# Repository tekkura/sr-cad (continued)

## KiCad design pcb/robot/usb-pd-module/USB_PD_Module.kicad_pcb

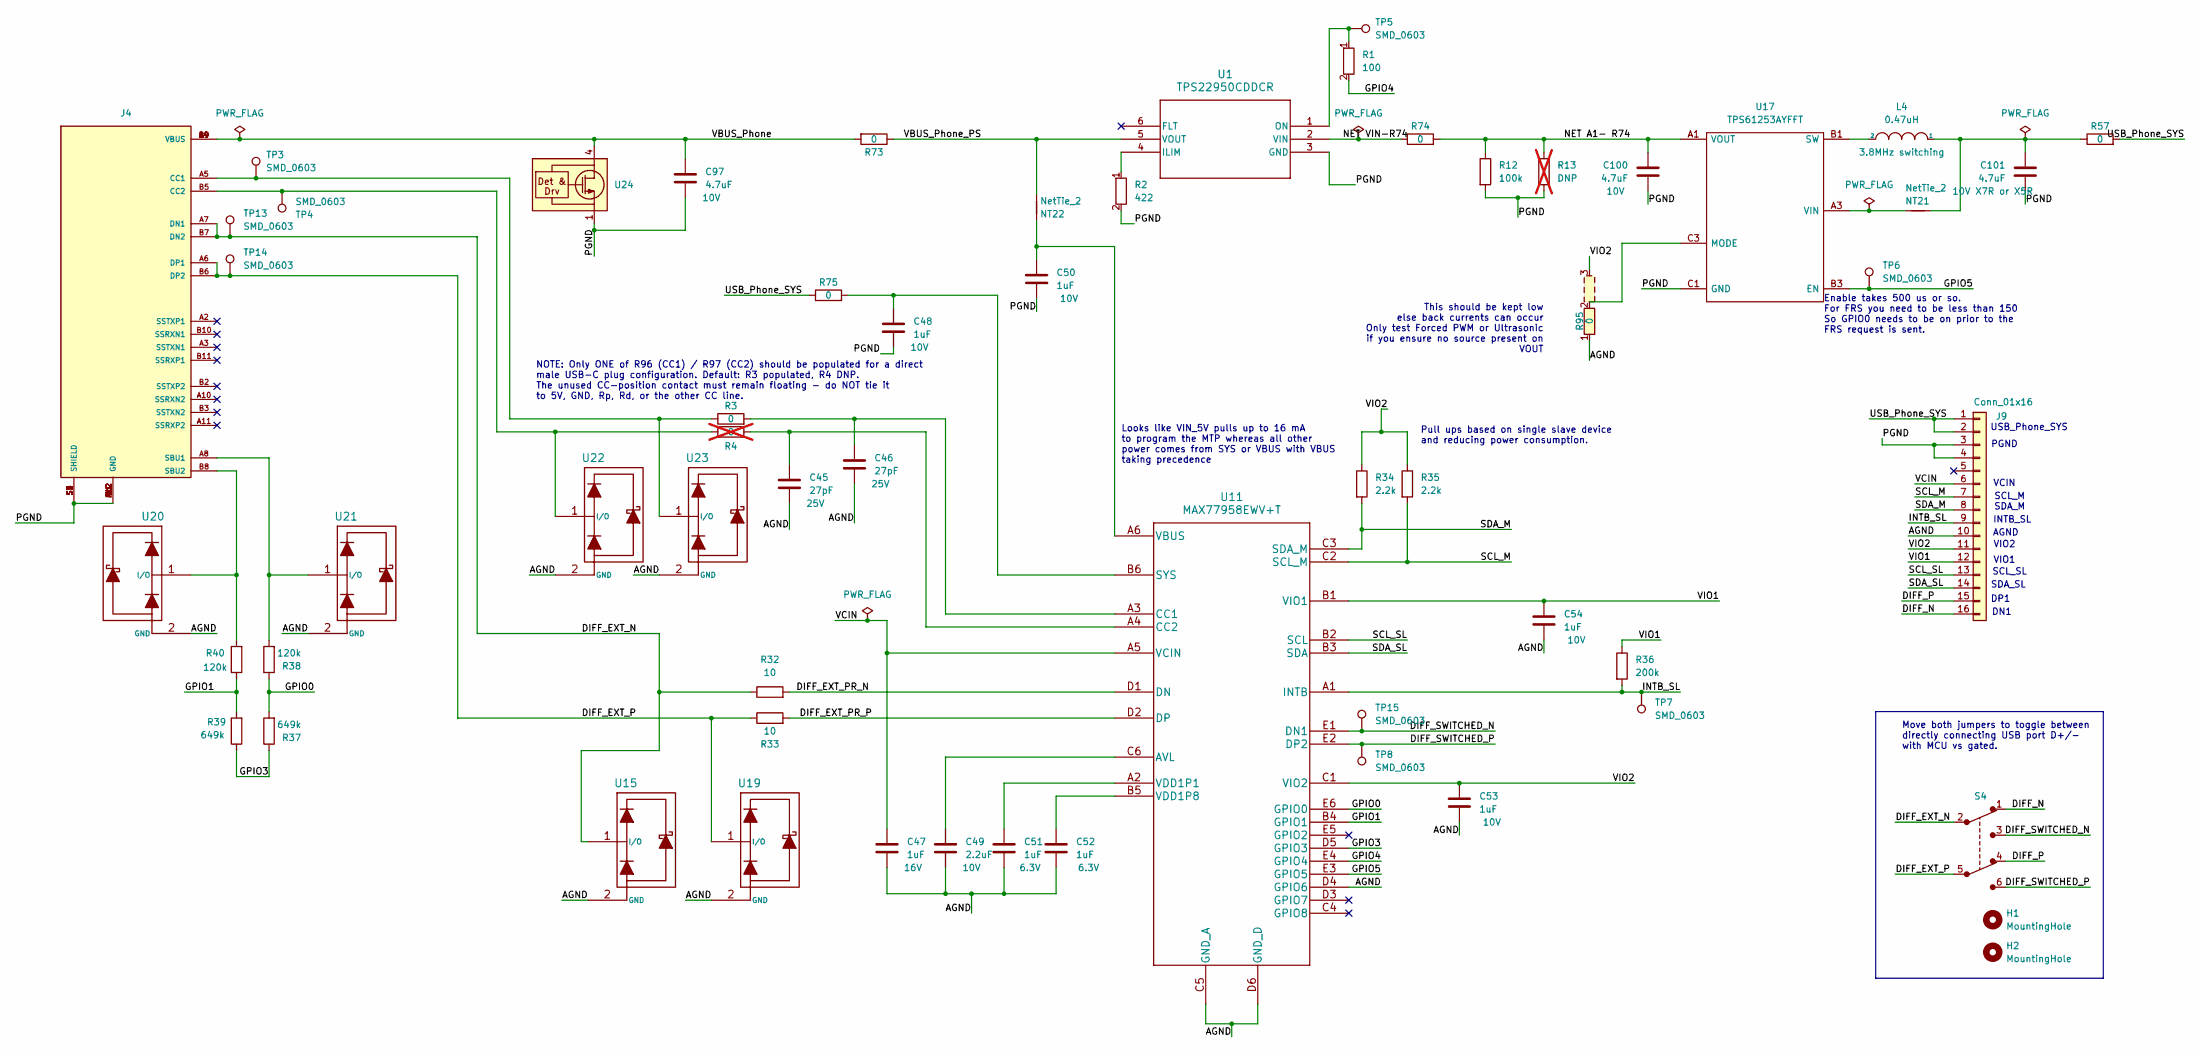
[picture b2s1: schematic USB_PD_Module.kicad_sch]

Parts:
C45, C46: 27pF; C_0402_1005Metric; Part Number GRM1555C1H270JA01J
C47, C48, C50, C51, C52, C53, C54: 1uF; C_0402_1005Metric; Part Number GRM155R61E105KA12D
C49: 2.2uF; C_0603_1608Metric; Part Number CL10A225KP8NNNC
C97, C100, C101: 4.7uF; C_0603_1608Metric; Part Number GRM188R61E475KE11D
H1, H2: MountingHole; MountingHole_2.2mm_M2_2mm_clearance
J4: USB4151-GF-C; GCT_USB4151-GF-C_REVA; Part Number USB4151-GF-C
J9: Conn_01x16; Castellated 1x16 2.54mm
L4: 0.47uH; Vishay-IHLP-2020BZ-FP_1.905x2.79-3D_2.0-0-0-MFG; Part Number IHLP2020BZERR47M01
NT21, NT22: NetTie_2; NetTie-_SMD_Pad6mil; Part Number N/A
R1: 100; R_0402_1005Metric; DigiKey_Part_Number 311-100LRCT-ND
R2: 422; R_0402_1005Metric; DigiKey_Part_Number YAG3158CT-ND
R3, R57, R75: 0; R_0603_1608Metric; Part Number RMCF0603ZT0R00
R4: 0; R_0603_1608Metric; Part Number RMCF0603ZT0R00; not fitted
R12: 100k; R_0603_1608Metric; Part Number WR06X1003FTL
R13: DNP; R_0603_1608Metric; Part Number DNP; not fitted
R32, R33: 10; R_0402_1005Metric; Part Number RC0402FR-1310RL
R34, R35: 2.2k; R_0603_1608Metric; Part Number RMCF0603JT2K20
R36: 200k; R_0603_1608Metric; Part Number RMCF0603JT200K
R37, R39: 649k; R_0603_1608Metric; Part Number ERJ-3EKF6493V
R38, R40: 120k; R_0603_1608Metric; Part Number RMCF0603JT120K
R73, R74: 0; R_0805_2012Metric; Part Number RMCF0805ZT0R00
R95: 0; R_0603_1608Metric_3pin_Switch; Part Number RMCF0603ZT0R00
S4: JS202011JCQN; SW_JS202011JCQN; Part Number JS202011JCQN
TP3, TP4, TP5, TP6, TP7, TP8, TP13, TP14, TP15: SMD_0603; TestPoint_SMD_0603; Part Number RCUCTE
U1: TPS22950CDDCR; DDC6_TEX
U11: MAX77958EWV+T; MAX77958EWV&plus_T; Part Number MAX77958EWV+T
U15, U19, U20, U21, U22, U23: TPD1E05U06; TPD1E05U06DPYR; Part Number TPD1E05U06DPYR
U17: TPS61253AYFFT; Texas_Instruments-YFF0009-BGA9C40P3X3_119X129X62; Part Number TPS61253AYFFT
U24: TVS0500DRV; TVS0500DRVR; Part Number TVS0500DRVR

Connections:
/AGND: C45.2, C46.2, C47.2, C49.2, C51.2, C52.2, C53.2, C54.2, J9.10, R95.1, U11.C5 (GND_A), U11.D4 (GPIO6), U11.D6 (GND_D), U15.2 (GND), U19.2 (GND), U20.2 (GND), U21.2 (GND), U22.2 (GND), U23.2 (GND)
/DIFF_EXT_N: J4.A7 (DN1), J4.B7 (DN2), R32.1, S4.2, TP13.1, U15.1 (I/O)
/DIFF_EXT_P: J4.A6 (DP1), J4.B6 (DP2), R33.1, S4.5, TP14.1, U19.1 (I/O)
/DIFF_EXT_PR_N: R32.2, U11.D1 (DN)
/DIFF_EXT_PR_P: R33.2, U11.D2 (DP)
/DIFF_N: J9.16, S4.1
/DIFF_P: J9.15, S4.4
/DIFF_SWITCHED_N: S4.3, TP15.1, U11.E1 (DN1)
/DIFF_SWITCHED_P: S4.6, TP8.1, U11.E2 (DP2)
/GPIO0: R37.2, R38.1, U11.E6 (GPIO0)
/GPIO1: R39.2, R40.1, U11.B4 (GPIO1)
/GPIO3: R37.1, R39.1, U11.D5 (GPIO3)
/GPIO4: R1.2, U11.E4 (GPIO4)
/GPIO5: TP6.1, U11.E3 (GPIO5), U17.B3 (EN)
/INTB_SL: J9.9, R36.2, TP7.1, U11.A1 (INTB)
/NET A1- R74: C100.1, R12.1, R13.1, R74.2, U17.A1 (VOUT), U17.A2 (VOUT)
/NET VIN-R74: R74.1, U1.2 (VIN)
/SCL_M: J9.7, R35.2, U11.C2 (SCL_M)
/SCL_SL: J9.13, U11.B2 (SCL)
/SDA_M: J9.8, R34.2, U11.C3 (SDA_M)
/SDA_SL: J9.14, U11.B3 (SDA)
/USB_Phone_SYS: J9.1, J9.2, R57.2, R75.1
/VBUS_Phone: C97.1, J4.A4 (VBUS), J4.A9 (VBUS), J4.B4 (VBUS), J4.B9 (VBUS), R73.2, U24.4 (IN), U24.5 (IN), U24.6 (IN)
/VBUS_Phone_PS: NT22.2, R73.1, U1.5 (VOUT)
/VCIN: C47.1, J9.6, U11.A5 (VCIN)
/VIO1: C54.1, J9.12, R36.1, U11.B1 (VIO1)
/VIO2: C53.1, J9.11, R34.1, R35.1, R95.3, U11.C1 (VIO2)
GND: C48.2, C50.2, C97.2, C100.2, C101.2, J4.A1 (GND), J4.A12 (GND), J4.B1 (GND), J4.B12 (GND), J4.S1 (SHIELD), J4.S2 (SHIELD), J4.S3 (SHIELD), J4.S4 (SHIELD), J4.S5 (SHIELD), J9.3, J9.4, R2.2, R12.2, R13.2, U1.3 (GND), U17.C1 (GND), U17.C2 (GND), U24.1 (GND), U24.2 (GND), U24.3 (GND), U24.7 (GND)
unnamed: C101.1, L4.1, NT21.2, R57.1
unnamed: J4.A5 (CC1), R3.1, TP3.1, U23.1 (I/O)
unnamed: J4.B5 (CC2), R4.1, TP4.1, U22.1 (I/O)
unnamed: J4.A8 (SBU1), R38.2, U21.1 (I/O)
unnamed: J4.B8 (SBU2), R40.2, U20.1 (I/O)
unnamed: L4.2, U17.B1 (SW), U17.B2 (SW)
unnamed: R2.1, U1.4 (ILIM)
unnamed: R1.1, TP5.1, U1.1 (ON)
unnamed: C49.1, U11.C6 (AVL)
unnamed: C46.1, R3.2, U11.A3 (CC1)
unnamed: C45.1, R4.2, U11.A4 (CC2)
unnamed: C48.1, R75.2, U11.B6 (SYS)
unnamed: C50.1, NT22.1, U11.A6 (VBUS)
unnamed: C51.1, U11.A2 (VDD1P1)
unnamed: C52.1, U11.B5 (VDD1P8)
unnamed: R95.2, U17.C3 (MODE)
unnamed: NT21.1, U17.A3 (VIN)

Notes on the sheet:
This should be kept low else back currents can occur Only test Forced PWM or Ultrasonic if you ensure no source present on VOUT
SCL_M
SCL_SL
SDA_M
AGND
VIO2
PGND
USB_Phone_SYS
DP1
INTB_SL
Enable takes 500 us or so. For FRS you need to be less than 150 So GPIO0 needs to be on prior to the FRS request is sent.
VCIN
NOTE: Only ONE of R96 (CC1) / R97 (CC2) should be populated for a direct male USB-C plug configuration. Default: R3 populated, R4 DNP. The unused CC-position contact must remain floating - do NOT tie it to 5V, GND, Rp, Rd, or the other CC line.
Pull ups based on single slave device and reducing power consumption.
DN1
SDA_SL
VIO1
Looks like VIN_5V pulls up to 16 mA to program the MTP whereas all other power comes from SYS or VBUS with VBUS taking precedence
Move both jumpers to toggle between directly connecting USB port D+/- with MCU vs gated.

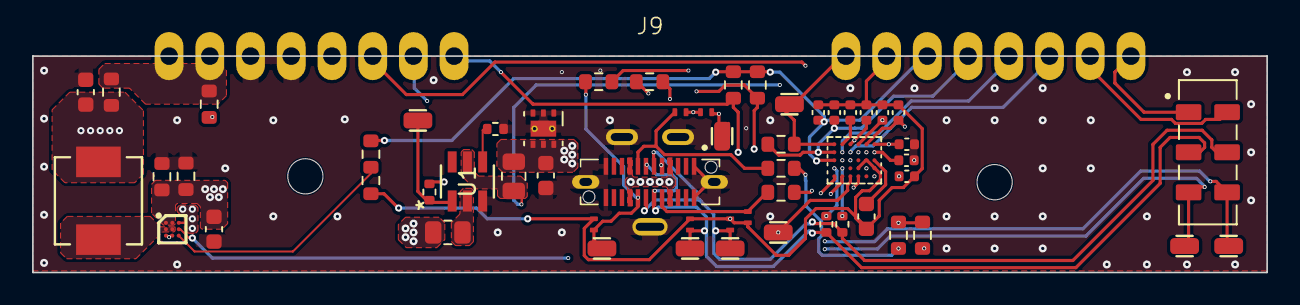
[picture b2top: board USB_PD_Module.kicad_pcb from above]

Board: 4 copper layers, 77.0 x 13.5 mm, 60 parts (0 on the bottom side), 45 nets.

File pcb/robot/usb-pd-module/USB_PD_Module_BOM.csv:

Reference;Qty;Part Number;Value;Footprint;Manufacturer
C45,C46;2;GRM1555C1H270JA01J;27pF;robot:C_0402_1005Metric;Murata
C47,C48,C50,C51,C52,C53,C54;7;GRM155R61E105KA12D;1uF;robot:C_0402_1005Metric;Murata
C49;1;CL10A225KP8NNNC;2.2uF;robot:C_0603_1608Metric;Samsung
C97,C100,C101;3;GRM188R61E475KE11D;4.7uF;robot:C_0603_1608Metric;Murata
J4;1;USB4151-GF-C;USB4151-GF-C;robot:GCT_USB4151-GF-C_REVA;GCT
L4;1;IHLP2020BZERR47M01;0.47uH;robot:Vishay-IHLP-2020BZ-FP_1.905x2.79-3D_2.0-0-0-MFG;Vishay
R12;1;WR06X1003FTL;100k;robot:R_0603_1608Metric;Walsin Technology
R32,R33;2;RC0402FR-1310RL;10;robot:R_0402_1005Metric;Yageo
R34,R35;2;RMCF0603JT2K20;2.2k;robot:R_0603_1608Metric;Stackpole Electronics
R36;1;RMCF0603JT200K;200k;robot:R_0603_1608Metric;Stackpole Electronics
R37,R39;2;ERJ-3EKF6493V;649k;robot:R_0603_1608Metric;Panasonic
R38,R40;2;RMCF0603JT120K;120k;robot:R_0603_1608Metric;Stackpole Electronics
R57,R75;2;RMCF0603ZT0R00;0;robot:R_0603_1608Metric;Stackpole Electronics
R65;1;AC0603JR-0710ML;10M;robot:R_0603_1608Metric;Yageo
R73,R74;2;RMCF0805ZT0R00;0;robot:R_0805_2012Metric;Stackpole Electronics
R95;1;RMCF0603ZT0R00;0;robot:R_0603_1608Metric_3pin_Switch;Stackpole Electronics
S4;1;JS202011JCQN;JS202011JCQN;robot:SW_JS202011JCQN;C&K
TP3,TP4,TP5,TP6,TP7,TP8,TP13,TP14,TP15;9;RCUCTE;SMD_0603;robot:TestPoint_SMD_0603;KOA Speer Electronics, Inc.
U11;1;MAX77958EWV+T;MAX77958EWV+T;robot:MAX77958EWV&plus_T;Maxim
U15,U19,U20,U21,U22,U23;6;TPD1E05U06DPYR;TPD1E05U06;robot:TPD1E05U06DPYR;Texas Instruments
U16;1;fpf1048bucx;fpf1048bucx;robot:BGA6N50P3X2_146X96X62N;onsemi
U17;1;TPS61253AYFFT;TPS61253AYFFT;robot:Texas_Instruments-YFF0009-BGA9C40P3X3_119X129X62;Texas Instruments
U24;1;TVS0500DRVR;TVS0500DRV;robot:TVS0500DRVR;Texas Instruments

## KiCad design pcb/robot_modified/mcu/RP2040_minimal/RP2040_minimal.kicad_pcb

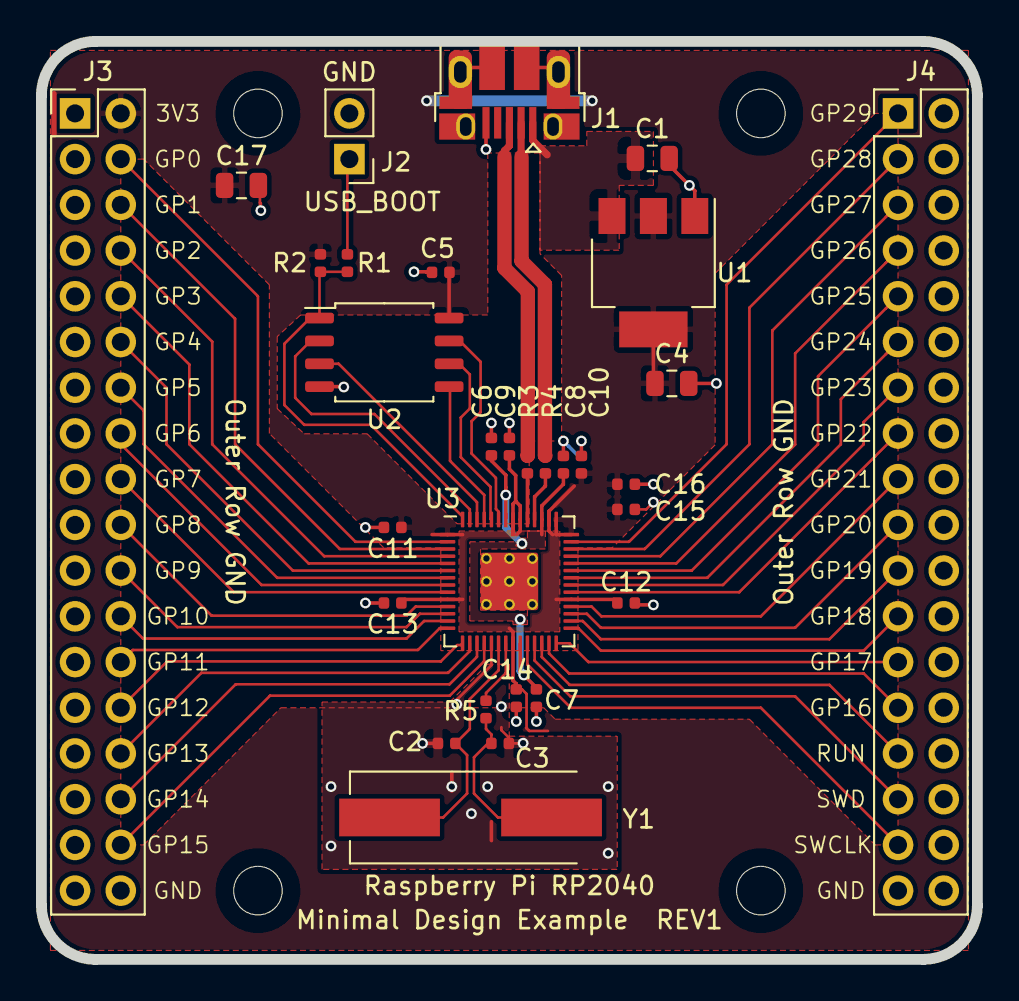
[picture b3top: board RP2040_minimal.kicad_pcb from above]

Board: 2 copper layers, 52.0 x 51.0 mm, 34 parts (0 on the bottom side), 51 nets.

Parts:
C1, C4, C17: 10u; C_0805_2012Metric
C2, C3: 27p; C_0402_1005Metric
C5, C6, C7, C9, C11, C12, C13, C14, C15, C16: 100n; C_0402_1005Metric
C8, C10: 1u; C_0402_1005Metric
H1, H2, H3, H4: MountingHole; MountingHole_2.7mm_M2.5
J1: USB_B_Micro; USB_Micro-B_Amphenol_10103594-0001LF_Horizontal_modified
J2: Conn_01x02; PinHeader_1x02_P2.54mm_Vertical
J3, J4: Conn_02x18_Odd_Even; PinHeader_2x18_P2.54mm_Vertical
R1, R5: 1k; C_0402_1005Metric
R2: DNF; C_0402_1005Metric
R3, R4: 27; C_0402_1005Metric
U1: NCP1117-3.3_SOT223; SOT-223-3_TabPin2
U2: W25Q128JVS; SOIC-8_5.23x5.23mm_P1.27mm
U3: RP2040; RP2040-QFN-56
Y1: ABLS-12.000MHZ-B4-T; Crystal_SMD_HC49-US

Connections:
+1V1: C6.1, C7.1, C8.1, U3.23, U3.45, U3.50
+3V3: C4.1, C5.1, C9.1, C10.1, C11.1, C12.1, C13.1, C14.1, C15.1, C16.1, C17.1, J3.2, R2.1, U1.2, U2.8, U3.1, U3.10, U3.22, U3.33, U3.42, U3.43, U3.44, U3.48, U3.49
/GPIO0: J3.4, U3.2
/GPIO1: J3.6, U3.3
/GPIO2: J3.8, U3.4
/GPIO3: J3.10, U3.5
/GPIO4: J3.12, U3.6
/GPIO5: J3.14, U3.7
/GPIO6: J3.16, U3.8
/GPIO7: J3.18, U3.9
/GPIO8: J3.20, U3.11
/GPIO9: J3.22, U3.12
/GPIO10: J3.24, U3.13
/GPIO11: J3.26, U3.14
/GPIO12: J3.28, U3.15
/GPIO13: J3.30, U3.16
/GPIO14: J3.32, U3.17
/GPIO15: J3.34, U3.18
/GPIO16: J4.27, U3.27
/GPIO17: J4.25, U3.28
/GPIO18: J4.23, U3.29
/GPIO19: J4.21, U3.30
/GPIO20: J4.19, U3.31
/GPIO21: J4.17, U3.32
/GPIO22: J4.15, U3.34
/GPIO23: J4.13, U3.35
/GPIO24: J4.11, U3.36
/GPIO25: J4.9, U3.37
/GPIO26_ADC0: J4.7, U3.38
/GPIO27_ADC1: J4.5, U3.39
/GPIO28_ADC2: J4.3, U3.40
/GPIO29_ADC3: J4.1, U3.41
/QSPI_SCLK: U2.6, U3.52
/QSPI_SD0: U2.5, U3.53
/QSPI_SD1: U2.2, U3.55
/QSPI_SD2: U2.3, U3.54
/QSPI_SD3: U2.7, U3.51
/QSPI_SS: R1.1, R2.2, U2.1, U3.56
/RUN: J4.29, U3.26
/SWCLK: J4.33, U3.24
/SWD: J4.31, U3.25
/USB_D+: J1.3, R3.1
/USB_D-: J1.2, R4.1
/XIN: C2.1, U3.20, Y1.1
/XOUT: R5.1, U3.21
/~USB_BOOT: J2.1, R1.2
GND: C1.2, C2.2, C3.2, C4.2, C5.2, C6.2, C7.2, C8.2, C9.2, C10.2, C11.2, C12.2, C13.2, C14.2, C15.2, C16.2, C17.2, J1.5, J1.6, J2.2, J3.1, J3.3, J3.5, J3.7, J3.9, J3.11, J3.13, J3.15, J3.17, J3.19, J3.21, J3.23, J3.25, J3.27, J3.29, J3.31, J3.33, J3.35, J3.36, J4.2, J4.4, J4.6, J4.8, J4.10, J4.12, J4.14, J4.16, J4.18, J4.20, J4.22, J4.24, J4.26, J4.28, J4.30, J4.32, J4.34, J4.35, J4.36, U1.1, U2.4, U3.19, U3.57
unnamed: C3.1, R5.2, Y1.2
unnamed: R3.2, U3.47
unnamed: R4.2, U3.46
VBUS: C1.1, J1.1, U1.3
